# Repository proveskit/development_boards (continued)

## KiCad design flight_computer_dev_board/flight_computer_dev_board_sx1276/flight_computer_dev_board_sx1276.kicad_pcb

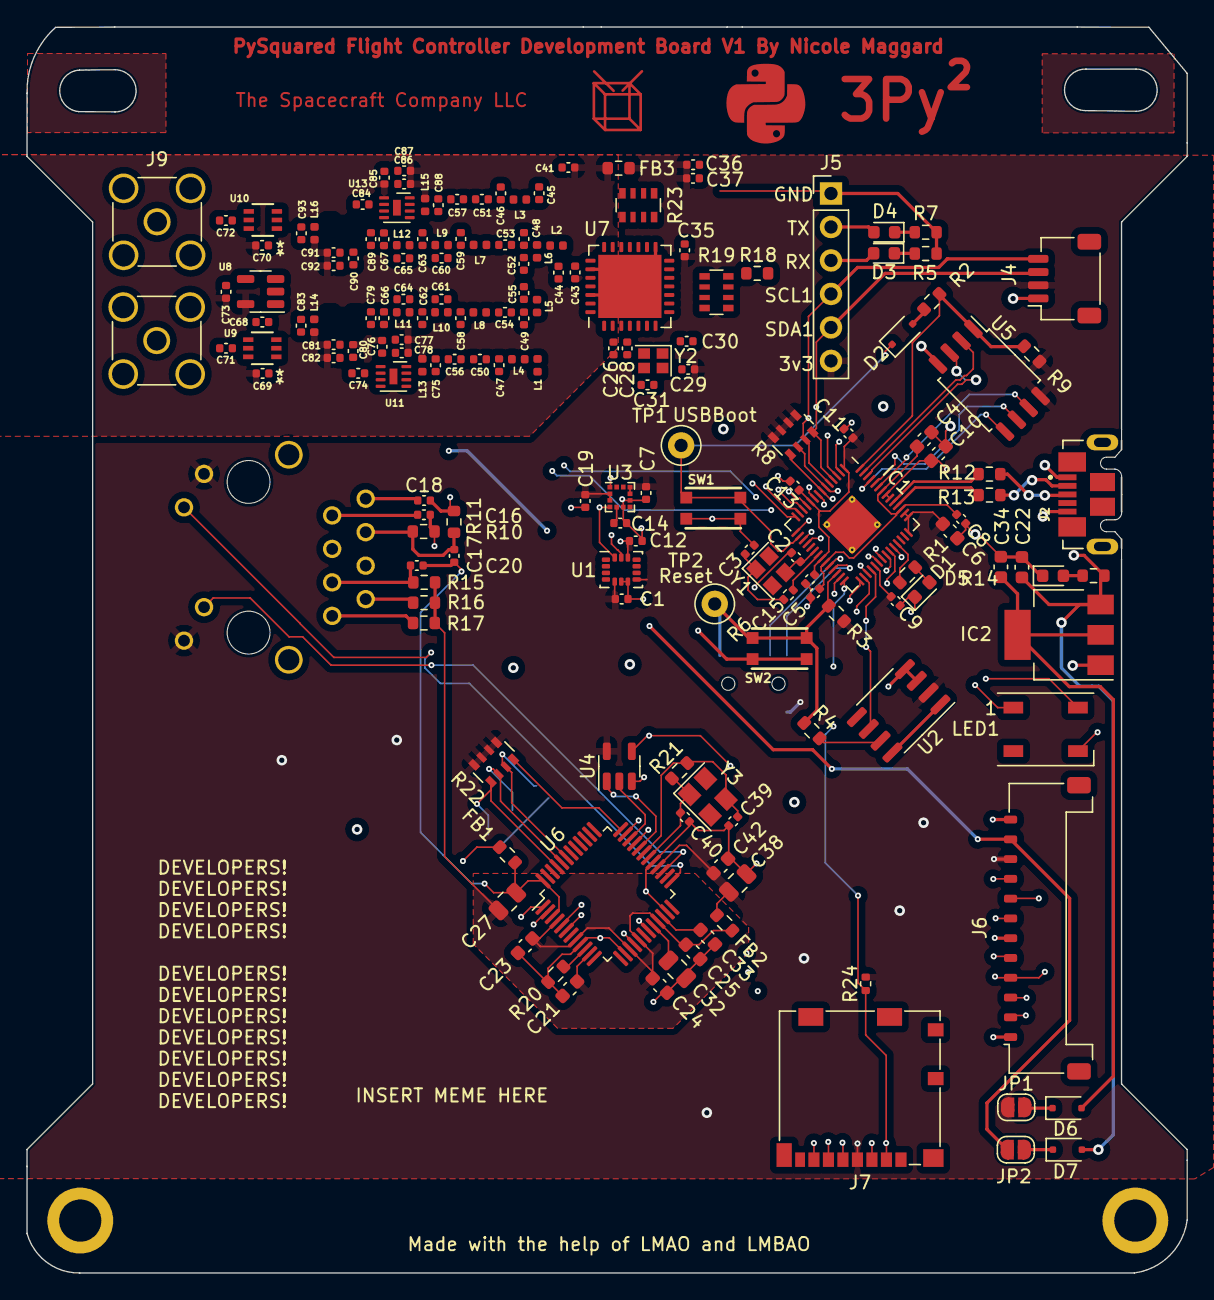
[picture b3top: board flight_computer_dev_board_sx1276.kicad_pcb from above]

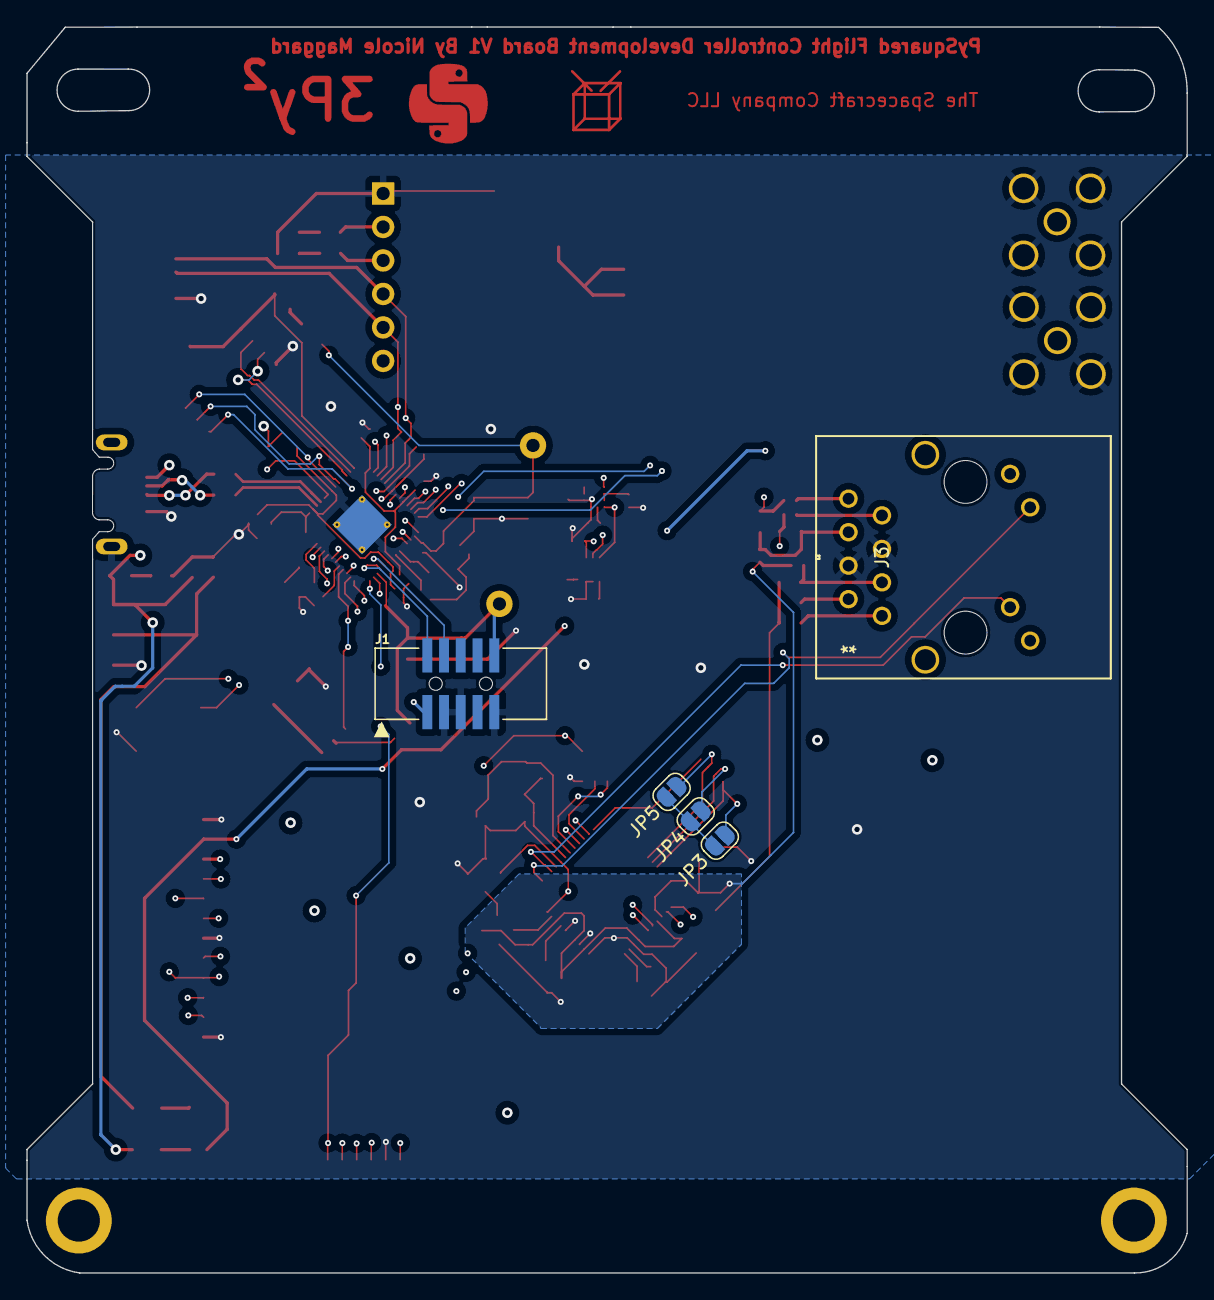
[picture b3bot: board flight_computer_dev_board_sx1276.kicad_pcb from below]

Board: 4 copper layers, 88.0 x 94.5 mm, 179 parts (5 on the bottom side), 132 nets.

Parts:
C1, C5, C6, C7, C9, C11, C12, C13, C15, C19, C26, C28, C29, C35, C43, C73, C79, C83, C89, C93: 100nf; C_0402_1005Metric
C2, C3, C39, C40: 22pF; C_0402_1005Metric
C4, C8, C10: 1uF; C_0603_1608Metric
C14: 220nf; C_0402_1005Metric
C16, C18: 6.8nf; C_0402_1005Metric
C17, C20, C44: 10nf; C_0402_1005Metric
C21, C23, C24, C25, C33, C42: 0.1uF; C_0603_1608Metric
C22: 10uF; C_0603_1608Metric
C27, C32, C38: 10uF; C_0805_2012Metric
C30, C31: 15pf; C_0402_1005Metric
C34: 22uF; C_0603_1608Metric
C36: 22uf; C_0402_1005Metric
C37, C41, C80, C90: 1uf; C_0402_1005Metric
C45, C46, C63: 3.3pf; C_0402_1005Metric
C47, C50, C51, C52, C55, C56, C57, C71, C72: 47pf; C_0402_1005Metric
C48: 8.2pf; C_0402_1005Metric
C49, C54: 4.7pf; C_0402_1005Metric
C53: 22pf; C_0402_1005Metric
C58, C59, C62, C66, C67: 6.8pf; C_0402_1005Metric
C60, C61, C64, C65: 2.7pf; C_0402_1005Metric
C68, C69, C70, C74, C75, C76, C77, C78, C81, C84, C85, C86, C87, C88, C91: 1nf; C_0402_1005Metric
C82, C92: 68pf; C_0402_1005Metric
D1, D3, D4, D5: LED; LED_0603_1608Metric
D2, D6, D7: NSR0320; D_SOD-323F
FB1, FB2, FB3: FerriteBead; R_0603_1608Metric
IC1: RP2040_QFN56; QFN-56-1EP_7x7mm_P0.4mm_EP3.2x3.2mm_ThermalVias
IC2: AZ1117CH-3.3TRG1; SOT-223
J1: Conn_ARM_JTAG_SWD_10; JTAG_2X05_1.27MM_BOX_NOCREAM
J2: USB_B_Micro; MOLEX_105164-0001
J3: RJ45_LED_Shielded; RB1-125BAG1A_WIZ
J4: Breakout; JST_SH_SM04B-SRSS-TB_1x04-1MP_P1.00mm_Horizontal
J5: Life Makes Lemonade; PinHeader_1x06_P2.54mm_Vertical
J6: FC to EPS Connector; Molex_Pico-Lock_504050-1291_1x12-1MP_P1.50mm_Horizontal
J7: 104031-0811; microSD_HC_Molex_104031-0811
J8, J9: Conn_Coaxial; SMA_Amphenol_901-144_Vertical
JP1, JP2, JP3, JP4, JP5: SolderJumper_2_Open; SolderJumper-2_P1.3mm_Open_RoundedPad1.0x1.5mm
L1: 18nH; L_0402_1005Metric
L2: 1.5nH; L_0402_1005Metric
L3: 10nH; L_0402_1005Metric
L4, L8: 15nH; L_0402_1005Metric
L5: 82nH; L_0402_1005Metric
L6: 33nH; L_0402_1005Metric
L7, L9, L12: 5.6nH; L_0402_1005Metric
L10, L11: 12nH; L_0402_1005Metric
L13, L15: 100nH; L_0402_1005Metric
L14, L16: 470nH; L_0402_1005Metric
LED1: WS2812B_SK6812_1515; LED_WS2812B_PLCC4_5.0x5.0mm_P3.2mm
R1, R3, R4, R9, R14: 10k; R_0603_1608Metric
R2, R5, R7, R18: 1k; R_0603_1608Metric
R6: 1k; R_0402_1005Metric
R8, R22: 10k; R_Array_Convex_4x0603
R10, R11, R16, R17: 49.9; R_0603_1608Metric
R12, R13: 22; R_0603_1608Metric
R15: 10; R_0603_1608Metric
R19, R23: 100; R_Array_Convex_4x0603
R20: 12.4k; R_0603_1608Metric
R21: 1M; R_0603_1608Metric
R24: 10k; R_0402_1005Metric
SW1, SW2: KMR2; BTN_KMR2_4.6X2.8
TP1: USBBOOT; TestPoint_Loop_D1.80mm_Drill1.0mm_Beaded
TP2: RESET; TestPoint_Loop_D1.80mm_Drill1.0mm_Beaded
U1: LSM6DSOTR; LGA-14_3x2.5mm_P0.5mm_LayoutBorder3x4y
U2: MAX706RESA; SO-8_3.9x4.9mm_P1.27mm
U3: LSM303AGRTR; LGA-12_2x2mm_P0.5mm
U4: SN74AHC1G125DBVR; SOT-23-5
U5: W25Q128JV; SOIC-8_5.275x5.275mm_P1.27mm
U6: W5500; LQFP-48_7x7mm_P0.5mm
U7: SX1276IMLTRT; QFN-28-1EP_6x6mm_P0.65mm_EP4.8x4.8mm
U8: 74LVC1G04W5-7; SOT-23-5
U9, U10: 4259-63; SC-70-6_PSM
U11, U13: TRF37A73IDSGR; DFN-8-1EP_2x2mm_P0.5mm_EP0.6x1.2mm
Y1: 12MHZ; Crystal_SMD_2520-4Pin_2.5x2.0mm
Y2: Crystal_GND24; Crystal_SMD_2016-4Pin_2.0x1.6mm
Y3: 25MHz; Crystal_SMD_3225-4Pin_3.2x2.5mm

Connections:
1.2V: C4.1, C5.2, C6.2, IC1.23 (DVDD), IC1.45 (VREG_VOUT), IC1.50 (DVDD)
3v3 Spec: C34.1, D6.2 (A), IC2.2 (OUTPUT), IC2.4 (VOUT)
+3.3VA: C41.1, C69.2, C70.2, C73.1, C76.2, C77.1, C78.1, C85.2, C86.1, C87.1, FB3.2, L13.2, L15.2, U8.5 (VCC), U9.6 (*CTRL/VDD), U10.6 (*CTRL/VDD), U11.1 (VCC), U13.1 (VCC)
+3V3: C1.1, C7.1, C8.1, C9.1, C10.1, C11.1, C12.1, C13.1, C15.1, C19.1, C29.1, C35.1, C36.1, C37.1, C38.1, C42.1, C43.1, FB2.1, FB3.1, IC1.1 (IOVDD), IC1.10 (IOVDD), IC1.22 (IOVDD), IC1.33 (IOVDD), IC1.42 (IOVDD), IC1.43 (ADC_IOVDD), IC1.44 (VREG_IOVDD), IC1.48 (USB_IOVDD), IC1.49 (IOVDD), J1.1 (VTref), J3.10, J3.12, J4.2, J5.6, J6.6, J6.10, J7.4 (VDD), JP1.1 (A), R3.1, R8.5 (R4.2), R8.6 (R3.2), R8.7 (R2.2), R8.8 (R1.2), R9.1, R22.5 (R4.2), R22.6 (R3.2), R22.7 (R2.2), R22.8 (R1.2), R24.2, U1.5 (VDDIO), U1.8 (VDD), U1.12 (CS), U2.2 (VCC), U3.2 (CS_XL), U3.3 (CS_MAG), U3.9 (VDD), U3.10 (VDD_IO), U4.5 (VCC), U5.8 (VCC), U6.28 (VDD), U7.4 (VR_DIG), U7.14 (VBAT_DIG), U7.24 (VBAT_RF)
/D+: IC1.47 (USB_D+), R12.1
/D-: IC1.46 (USB_D-), R13.1
/QSPI_CS: IC1.56 (~QSPI_CS), R2.1, R9.2, U5.1 (SSEL)
/QSPI_DATA[0]: IC1.53 (QSPI_SD0), U5.5 (MOSI)
/QSPI_DATA[1]: IC1.55 (QSPI_SD1), U5.2 (MISO)
/QSPI_DATA[2]: IC1.54 (QSPI_SD2), U5.3 (WP#/IO2)
/QSPI_DATA[3]: IC1.51 (QSPI_SD3), U5.7 (HOLD#/IO3)
/QSPI_SCK: IC1.52 (QSPI_SCLK), U5.6 (SCK)
/USBBOOT: D2.1 (K), IC1.16 (GPIO13), SW1.A, SW1.A' (P1), TP1.1
/~RESET: IC1.26 (/RUN), J1.10 (~RESET), R3.2, R4.1, SW2.A, SW2.A' (P1), TP2.1
BURN_RELAY_A: IC1.18 (GPIO15), J6.2
ENABLE_BURN: IC1.8 (GPIO6), J6.9
ENAB_RF: IC1.15 (GPIO12), J6.5
GND: C1.2, C2.1, C3.1, C4.2, C5.1, C6.1, C7.2, C8.2, C9.2, C10.2, C11.2, C12.2, C13.2, C14.2, C15.2, C19.2, C22.2, C26.2, C28.2, C29.2, C30.1, C31.2, C34.2, C35.2, C36.2, C37.2, C38.2, C39.2, C40.2, C41.2, C42.2, C43.2, C44.2, C45.2, C46.2, C47.2, C48.2, C49.2, C52.2, C55.2, C58.2, C59.2, C62.2, C63.2, C66.2, C67.2, C68.2, C69.1, C70.1, C73.2, C76.1, C77.2, C78.2, C80.1, C81.2, C82.2, C85.1, C86.2, C87.2, C90.1, C91.2, C92.2, D1.1 (K), D5.1 (K), FB1.1, IC1.57 (GND), IC2.1 (ADJ/GND), J1.3 (GND), J1.5 (GND), J1.9 (GNDDetect), J2.5 (GND), J2.SH1 (Shield), J3.4, J3.5, J4.1, J5.1, J6.1, J6.12, J7.6 (VSS), J8.2 (Ext), J9.2 (Ext), L1.1, LED1.3 (GND), R5.2, R7.2, SW1.B (S), SW1.B' (S1), SW2.B (S), SW2.B' (S1), U1.6 (GND), U1.7 (GND), U2.3 (GND), U2.4 (PFI), U3.6 (GND), U3.8 (GND), U4.3 (GND), U5.4 (VSS), U6.23 (RSVD), U6.29 (GND), U7.15 (GND), U7.23 (GND), U7.26 (GND), U7.29 (GND), U8.3 (GND), U9.2 (GND), U10.2 (GND), U11.3 (NC), U11.4 (NC), U11.5 (PWDN), U11.6 (NC), U11.8 (NC), U11.9 (GND), U13.3 (NC), U13.4 (NC), U13.5 (PWDN), U13.6 (NC), U13.8 (NC), U13.9 (GND), Y2.2, Y2.4
GNDA: C17.2, C20.2, C21.2, C23.2, C24.2, C25.2, C27.2, C32.1, C33.1, FB1.2, R20.1, U6.3 (AGND), U6.9 (AGND), U6.14 (AGND), U6.16 (AGND), U6.19 (AGND), U6.48 (AGND)
GREENLED: J3.11, U6.25 (LINKLED)
HIGH_IN1: C84.1, U10.3 (RF2)
HIGH_IN2: C57.2, C88.2
HIGH_OUT1: C65.2, C67.1, C89.1, L12.2
HIGH_OUT2: C93.2, U10.1 (RF1)
I2C_RESET: IC1.9 (GPIO7), J6.4
LOW_IN1: C74.1, U9.1 (RF1)
LOW_IN2: C56.2, C75.2
LOW_OUT1: C64.2, C66.1, C79.1, L11.2
LOW_OUT2: C83.2, U9.3 (RF2)
MISO_ETHER: U4.2 (A), U6.34 (MISO)
NEOPIX: IC1.36 (GPIO24), LED1.4 (DI)
NEO_PWR: IC1.37 (GPIO25), LED1.1 (VDD)
unnamed: C3.2, R6.2, Y1.1
unnamed: C16.1, J3.7
unnamed: C18.1, J3.8
unnamed: C46.1, C51.1, L3.2
unnamed: C47.1, C50.1, L4.2
unnamed: C48.1, C53.1, L2.1, L6.1
unnamed: C50.2, C56.1
unnamed: C51.2, C57.1
unnamed: C53.2, L7.1
unnamed: C54.2, L8.1
unnamed: C58.1, C61.1, L8.2, L10.1
unnamed: C59.1, C60.1, L7.2, L9.1
unnamed: C60.2, C63.1, C65.1, L9.2, L12.1
unnamed: C61.2, C62.1, C64.1, L10.2, L11.1
unnamed: D1.2 (A), R1.2
unnamed: D2.2 (A), R2.2
unnamed: D3.1 (K), R5.1
unnamed: D4.1 (K), R7.1
unnamed: D5.2 (A), R14.2
unnamed: D6.1 (K), JP1.2 (B)
unnamed: D7.1 (K), JP2.2 (B)
unnamed: C2.2, IC1.20 (XIN), Y1.3 (2)
unnamed: IC1.21 (XOUT), R6.1
unnamed: C71.2, J8.1 (In)
unnamed: C72.2, J9.1 (In)
unnamed: JP3.1 (A), JP4.1 (A), JP5.1 (A)
unnamed: JP3.2 (B), R22.1 (R1.1), U6.45 (PMODE0)
unnamed: JP4.2 (B), R22.2 (R2.1), U6.44 (PMODE1)
unnamed: JP5.2 (B), R22.3 (R3.1), U6.43 (PMODE2)
unnamed: R19.2 (R2.1), U7.12 (DIO4)
unnamed: R19.3 (R3.1), U7.8 (DOI0)
unnamed: R19.4 (R4.1), U7.7 (NRESET)
unnamed: R22.4 (R4.1), U6.36 (INTN)
unnamed: R23.8 (R1.2), U7.16 (SCK)
unnamed: R23.7 (R2.2), U7.17 (MISO)
unnamed: R23.6 (R3.2), U7.18 (MOSI)
unnamed: R23.5 (R4.2), U7.19 (NSS)
unnamed: U2.1 (~MR), U2.8 (~WDO)
unnamed: R4.2, U2.7 (~RESET)
unnamed: C14.1, U3.5 (C1)
unnamed: C33.2, U6.22 (1V20)
unnamed: R20.2, U6.10 (EXRES1)
unnamed: C32.2, U6.20 (TOCAP)
unnamed: C40.1, R21.1, U6.30 (XI/CLKIN), Y3.1
unnamed: C39.1, R21.2, U6.31 (XO), Y3.3 (2)
unnamed: C28.1, U7.3 (VBAT_ANA)
unnamed: C26.1, U7.2 (VR_ANA)
unnamed: C30.2, U7.5 (XTA), Y2.3
unnamed: C31.1, U7.6 (XTB), Y2.1
unnamed: C68.1, U8.4 (Y), U9.4 (CTRL)
unnamed: C71.1, U9.5 (RFC)
unnamed: C72.1, U10.5 (RFC)
unnamed: C74.2, U11.2 (RFIN)
unnamed: C75.1, L13.1, U11.7 (RFOUT)
unnamed: C93.1, L16.1
unnamed: C84.2, U13.2 (RFIN)
unnamed: C88.1, L15.1, U13.7 (RFOUT)
unnamed: C83.1, L14.1
PA_BOOST: L2.2, U7.27 (PA_BOOST)
RCT: C17.1, J3.6, R10.2, R11.2
RF1_IO0: IC1.35 (GPIO23), R19.6 (R3.2)
RF1_IO4: IC1.34 (GPIO22), R19.7 (R2.2)
RF1_RST: IC1.31 (GPIO20), R19.5 (R4.2)
RFI_HF: C45.1, L3.1, U7.21 (RFI_HF)
RFI_LF: L1.2, L4.1, U7.1 (RFI_LF)
RFO_LF: C49.1, C54.1, L5.2, U7.28 (RFO_LF)
RF_CONTROL: IC1.40 (GPIO28/AD2), R18.1, R19.8 (R1.2)
RF_CONTROL_SW: R19.1 (R1.1), U8.2 (A), U10.4 (CTRL)
RX: D3.2 (A), IC1.3 (GPIO1), J5.3
RX+: C16.2, R10.1, U6.6 (RXP)
RX-: C18.2, R11.1, U6.5 (RXN)
SCL0: IC1.7 (GPIO5), J6.7, R8.1 (R1.1)
SCL1: IC1.5 (GPIO3), J4.4, J5.4, R8.3 (R3.1), U1.13 (SCL), U3.1 (SCL/SPC)
SDA0: IC1.6 (GPIO4), J6.8, R8.2 (R2.1)
SDA1: IC1.4 (GPIO2), J4.3, J5.5, R8.4 (R4.1), U1.14 (SDA), U3.4 (SDA/SDI/SDO)
SPI0_CS0: IC1.28 (GPIO17), J7.2 (CD/DAT3), R24.1
SPI0_CS1: IC1.38 (GPIO26/AD0), U4.1 (*OE), U6.32 (SCSN)
SPI0_MISO: IC1.27 (GPIO16), J7.7 (DAT0), U4.4 (Y)
SPI0_MOSI: IC1.30 (GPIO19), J7.3 (CMD), U6.35 (MOSI)
SPI0_SCK: IC1.29 (GPIO18), J7.5 (CLK), U6.33 (SCLK)
SPI1_CS0: IC1.12 (GPIO9), R23.4 (R4.1)
SPI1_MISO: IC1.11 (GPIO8), R23.2 (R2.1)
SPI1_MOSI: IC1.14 (GPIO11), R23.3 (R3.1)
SPI1_SCK: IC1.13 (GPIO10), R23.1 (R1.1)
SWCLK: IC1.24 (SWCLK), J1.4 (SWDCLK/TCK)
SWDIO: IC1.25 (SWDIO), J1.2 (SWDIO/TMS)
TCT: C20.1, J3.3, R15.2
TX: D4.2 (A), IC1.2 (GPIO0), J5.2
TX+: J3.1, R17.2, U6.2 (TXP)
TX-: J3.2, R16.2, U6.1 (TXN)
USB_D+: J2.3 (D+), R12.2
USB_D-: J2.2 (D-), R13.2
VBUS: C22.1, D7.2 (A), IC2.3 (INPUT), J2.1 (VBUS), R14.1
VBUS_RESET: IC1.17 (GPIO14), J6.3
VCC_RF1: C80.2, C81.1, C82.1, C90.2, C91.1, C92.1, J6.11, JP2.1 (A), L14.2, L16.2
VDDA: C21.1, C23.1, C24.1, C25.1, C27.1, FB2.2, R15.1, R16.1, R17.1, U6.4 (AVDD), U6.8 (AVDD), U6.11 (AVDD), U6.15 (AVDD), U6.17 (AVDD), U6.21 (AVDD)
VR_PA: C44.1, C52.1, C55.1, L5.1, L6.2, U7.25 (VR_PA)
WDT_WDI: IC1.32 (GPIO21), U2.6 (~WDI)
YELLOWLED: J3.9, U6.27 (ACTLED)
firm_active: IC1.39 (GPIO27/AD1), R1.1
